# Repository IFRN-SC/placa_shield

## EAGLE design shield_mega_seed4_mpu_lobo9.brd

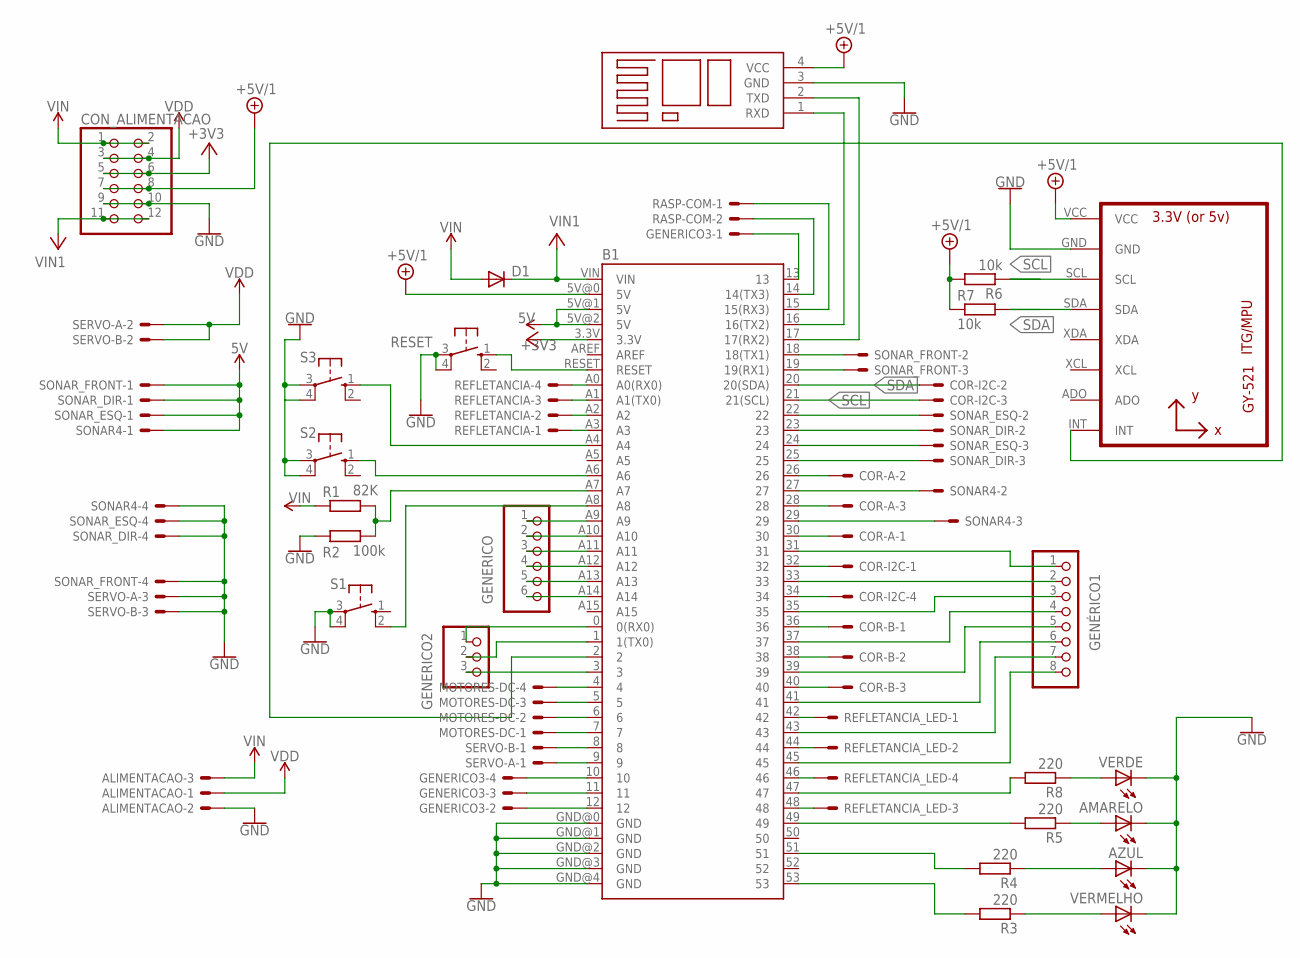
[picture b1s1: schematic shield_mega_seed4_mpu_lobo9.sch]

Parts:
ALIMENTACAO: 22-23-2031
AMARELO: LED5MM
AZUL: LED5MM
B1: ARDUINO_MEGA_R3FULL; ARDUINO_MEGA
B2: BLUETOOTH
CON_ALIMENTACAO: PINHD-2X6; 2X06
COR-A: 22-23-2031
COR-B: 22-23-2031
COR-I2C: 22-23-2041
D1: 1N4004; DO41-10
GENERICO: PINHD-1X6; 1X06
GENERICO2: PINHD-1X3; 1X03
GENERICO3: 22-23-2041
GENÉRICO1: PINHD-1X8; 1X08
MOTORES-DC: 22-23-2041
R1: 82K; 0204/7
R2: 100k; 0204/7
R3, R4, R5, R8: 220; 0207/7
R6, R7: 10k; 0204/7
RASP-COM: 22-23-2021
REFLETANCIA: 22-23-2041
REFLETANCIA_LED: 22-23-2041
RESET: 10-XX; B3F-10XX
S1, S2, S3: 10-XX; B3F-10XX
SERVO-A: 22-23-2031
SERVO-B: 22-23-2031
SONAR4: 22-23-2041
SONAR_DIR: 22-23-2041
SONAR_ESQ: 22-23-2041
SONAR_FRONT: 22-23-2041
U1: GY-521MPU6050; GY-521
VERDE: LED5MM
VERMELHO: LED5MM

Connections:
5V: B1.5V@1 (5V), B1.5V@2 (5V), SONAR4.1, SONAR_DIR.1, SONAR_ESQ.1, SONAR_FRONT.1
+3V3: B1.3.3V, CON_ALIMENTACAO.5, CON_ALIMENTACAO.6
+5V/1: B1.5V@0 (5V), B2.4 (VCC), CON_ALIMENTACAO.7, CON_ALIMENTACAO.8, R6.2, R7.1, U1.VCC
GND: ALIMENTACAO.2, AMARELO.K (C), AZUL.K (C), B1.GND@0 (GND), B1.GND@1 (GND), B1.GND@2 (GND), B1.GND@3 (GND), B1.GND@4 (GND), B2.3 (GND), CON_ALIMENTACAO.9, CON_ALIMENTACAO.10, R2.1, RESET.3, RESET.4 (P1), S1.3, S1.4 (P1), S2.3, S2.4 (P1), S3.3, S3.4 (P1), SERVO-A.3, SERVO-B.3, SONAR4.4, SONAR_DIR.4, SONAR_ESQ.4, SONAR_FRONT.4, U1.GND, VERDE.K (C), VERMELHO.K (C)
unnamed: B1.A2, REFLETANCIA.2
unnamed: B1.A3, REFLETANCIA.1
unnamed: B1.4, MOTORES-DC.4
unnamed: B1.5, MOTORES-DC.3
unnamed: B1.6, MOTORES-DC.2
unnamed: B1.7, MOTORES-DC.1
unnamed: B1.8, SERVO-B.1
unnamed: B1.9, SERVO-A.1
unnamed: B1.14 (14(TX3)), RASP-COM.2
unnamed: B1.15 (15(RX3)), RASP-COM.1
unnamed: B1.19 (19(RX1)), SONAR_FRONT.3
unnamed: B1.18 (18(TX1)), SONAR_FRONT.2
unnamed: B1.16 (16(TX2)), B2.1 (RXD)
unnamed: B1.30, COR-A.1
unnamed: B1.26, COR-A.2
unnamed: B1.34, COR-I2C.4
unnamed: B1.36, COR-B.1
unnamed: B1.38, COR-B.2
unnamed: B1.40, COR-B.3
unnamed: B1.A7, R1.2, R2.2
unnamed: B1.51, R4.2
unnamed: B1.53, R3.2
unnamed: B1.49, R5.2
unnamed: AMARELO.A, R5.1
unnamed: AZUL.A, R4.1
unnamed: R3.1, VERMELHO.A
unnamed: B1.27, SONAR4.2
unnamed: B1.A6, S2.1 (S)
unnamed: B1.A1 (A1(TX0)), REFLETANCIA.3
unnamed: B1.29, SONAR4.3
unnamed: B1.RESET, RESET.1 (S)
unnamed: B1.0 (0(RX0)), GENERICO2.1
unnamed: B1.A0 (A0(RX0)), REFLETANCIA.4
unnamed: B1.25, SONAR_DIR.3
unnamed: B1.24, SONAR_ESQ.3
unnamed: B1.23, SONAR_DIR.2
unnamed: B1.22, SONAR_ESQ.2
unnamed: B1.47, R8.2
unnamed: B1.2, U1.INT
unnamed: B1.32, COR-I2C.1
unnamed: B1.28, COR-A.3
unnamed: R8.1, VERDE.A
unnamed: B1.17 (17(RX2)), B2.2 (TXD)
unnamed: B1.10, GENERICO3.4
unnamed: B1.12, GENERICO3.2
unnamed: B1.11, GENERICO3.3
unnamed: B1.13, GENERICO3.1
unnamed: B1.42, REFLETANCIA_LED.1
unnamed: B1.44, REFLETANCIA_LED.2
unnamed: B1.46, REFLETANCIA_LED.4
unnamed: B1.48, REFLETANCIA_LED.3
unnamed: B1.A14, GENERICO.6
unnamed: B1.A13, GENERICO.5
unnamed: B1.A12, GENERICO.4
unnamed: B1.A11, GENERICO.3
unnamed: B1.A10, GENERICO.2
unnamed: B1.A9, GENERICO.1
unnamed: B1.A8, S1.2 (S1)
unnamed: B1.A4, S3.1 (S)
unnamed: B1.31, GENÉRICO1.1
unnamed: B1.33, GENÉRICO1.2
unnamed: B1.35, GENÉRICO1.3
unnamed: B1.37, GENÉRICO1.4
unnamed: B1.39, GENÉRICO1.5
unnamed: B1.41, GENÉRICO1.6
unnamed: B1.43, GENÉRICO1.7
unnamed: B1.45, GENÉRICO1.8
unnamed: B1.1 (1(TX0)), GENERICO2.2
unnamed: B1.3, GENERICO2.3
SCL: B1.21 (21(SCL)), COR-I2C.3, R6.1, U1.SCL
SDA: B1.20 (20(SDA)), COR-I2C.2, R7.2, U1.SDA
V+: B1.VIN, CON_ALIMENTACAO.11, CON_ALIMENTACAO.12, D1.C
VDD: ALIMENTACAO.1, CON_ALIMENTACAO.3, CON_ALIMENTACAO.4, SERVO-A.2, SERVO-B.2
VIN: ALIMENTACAO.3, CON_ALIMENTACAO.1, CON_ALIMENTACAO.2, D1.A, R1.1

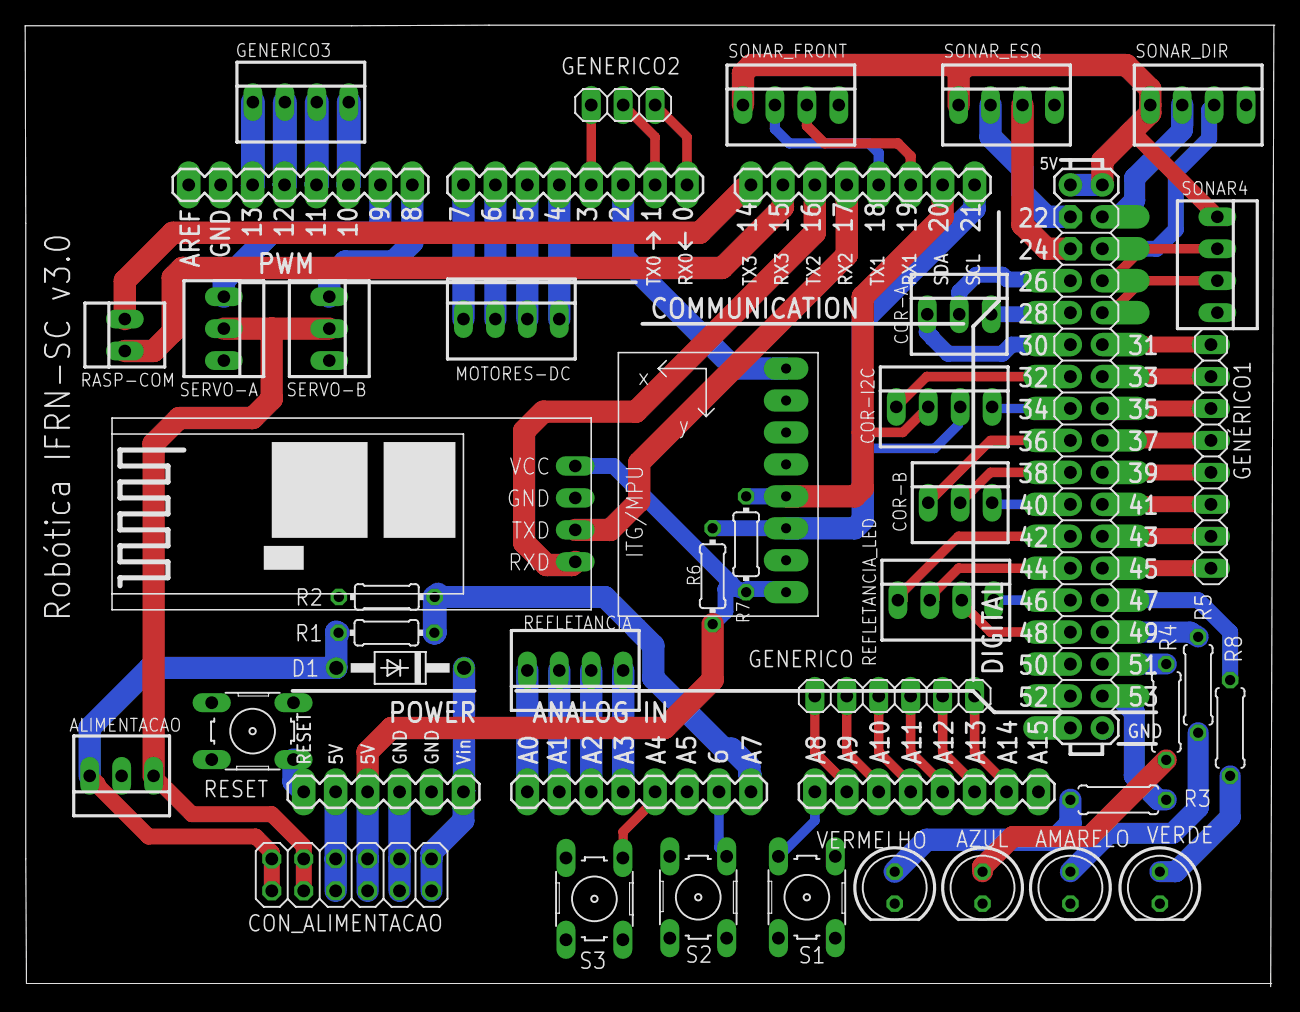
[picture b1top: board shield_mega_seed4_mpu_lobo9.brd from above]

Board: 2 copper layers, 99.4 x 76.5 mm, 39 parts (0 on the bottom side), 78 nets.

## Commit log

2018-07-02 Inicialização da placa shield
2018-07-02 Criação de gitignore
2018-07-02 mudança no label da versão
2018-07-02 Adição de módulo bluetooth; Remoção do buck; Remoção de conector XT-60; Remoção de conector da chave;
2018-07-02 Remoção do conector do multímetro; remoção do conector de alimentação do sensor de refletância; remoção do conector de alimentação do motor;
2018-07-02 remoção de erro que deixou o conector de alimentação sem terra
2018-07-02 Adição de terra em pino do botão de reset que estava faltando
2018-07-02 Remoção do conector de alimentação do raspberry PI
2018-07-02 Modificação de posição do conector do motor e conectores dos servo motores; modificação de posição do símbolo do IF
2018-07-02 Mudança no tamanho da placa.
2018-07-02 Modificação do tamanho mínimo da trilha de terra; Modificação de trilha que estava torta para ficar reta
2018-07-02 modificação da posição das resistências do divisor de tensão
2018-07-02 mudança de posição de fio
2019-03-19 Adicionado o conector para o novo modelo da placa.
2019-03-27 Adição de novos conectores
    Adição de conectorenectores genéricos
    Adição dos conectores de refletância de leds
    Modificação da posição dos conectores dos sensores de cor
2019-03-28 Mudança de botões
    mudança de posição nos botões
    adição de conectores genéricos
    adição de um quarto conector para sonares
2019-03-28 Adição de conectores
    Adição dos conectores de alimentação genéricos
2019-03-28 Adição de logo
    modificação de logo do IF
    adição na parte superior da placa de logos da robótica
    adição de imagens dos logos
2019-03-28 Adição de novo layer
    Adição de novo layer para os logos
    Organização de nomes dos componetes
    Pequena modificação do botões para alinha-los
2019-03-28 Adicionado arquivo cam
    Arquivo para gerar a placa industialmente através do site seedstudio

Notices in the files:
parts and their libraries:
SparkFun-Boards3: Licensing: Creative Commons ShareAlike 4.0 International - https://creativecommons.org/licenses/by-sa/4.0
